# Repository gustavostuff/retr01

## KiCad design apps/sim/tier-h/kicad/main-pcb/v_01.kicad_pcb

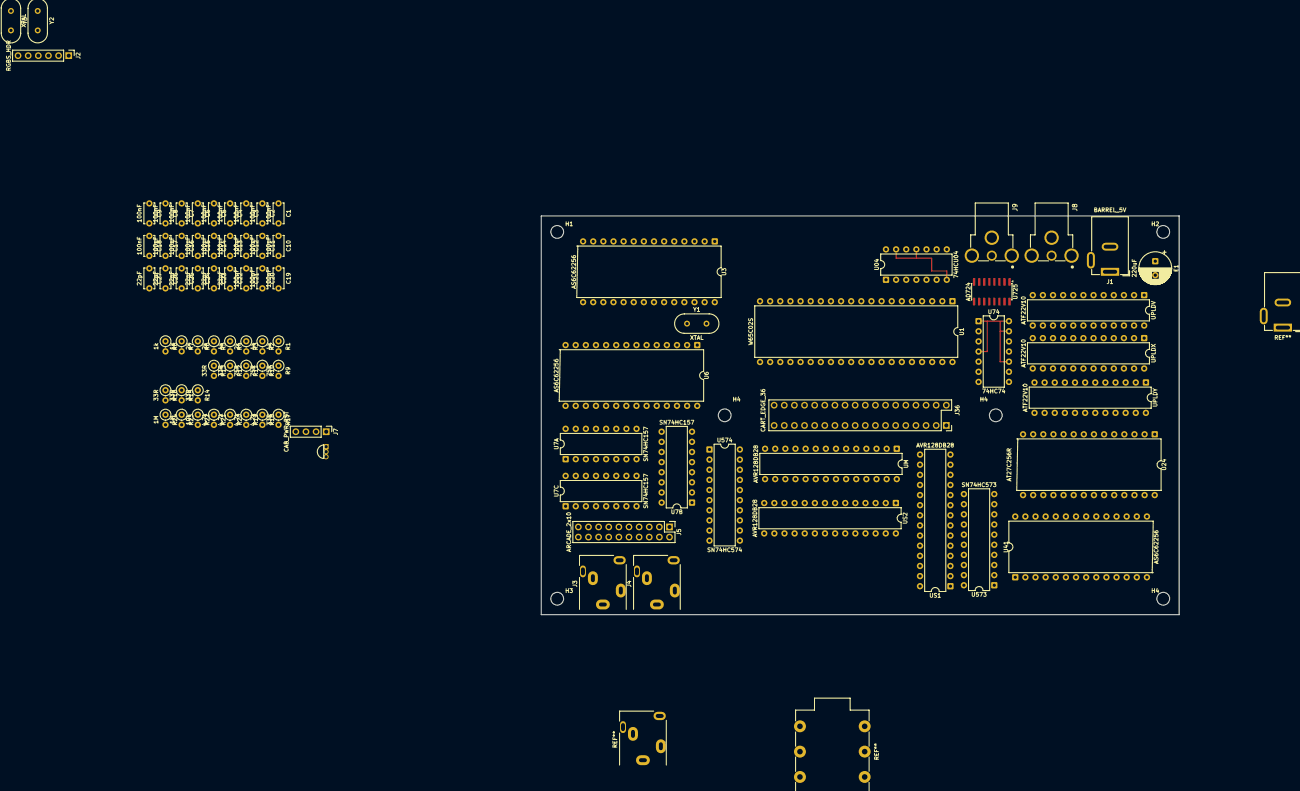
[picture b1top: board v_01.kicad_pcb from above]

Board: 2 copper layers, 160.0 x 100.0 mm, 90 parts (0 on the bottom side), 139 nets, no tracks yet.

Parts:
C1, C2, C3, C4, C5, C6, C7, C8, C9, C10, C11, C12, C13, C14, C15, C16, C17, C18, C19, C20, C21: 100nF; C_Disc_D5.0mm_W2.5mm_P5.00mm
C22, C23, C24, C25, C26, C27: 22pF; C_Disc_D5.0mm_W2.5mm_P5.00mm
E1: 220uF; CP_Radial_D8.0mm_P3.50mm
H1, H2, H3, H4, H4#2, H4#3: MountingHole_3.2mm_M3
J1: BARREL_5V; BarrelJack_GCT_DCJ200-10-A_Horizontal
J2: RGBS_HDR; PinHeader_1x06_P2.54mm_Vertical
J3: TRS_P1; Jack_3.5mm_CUI_SJ1-3515N_Horizontal
J4: TRS_P2; Jack_3.5mm_CUI_SJ1-3515N_Horizontal
J5: ARCADE_2x10; PinHeader_2x10_P2.54mm_Vertical
J7: CAB_PWR_RST; PinHeader_1x04_P2.54mm_Vertical
J8: RCJ-012; CUI_RCJ-014_Audio
J9: RCJ-014; CUI_RCJ-014
J36: CART_EDGE_36; EDAC_395_MoboSocket_2x18_2.54x5.08mm
R1, R2, R4: 4k; R_Axial_DIN0207_L6.3mm_D2.5mm_P2.54mm_Vertical
R3, R5, R6: 2k; R_Axial_DIN0207_L6.3mm_D2.5mm_P2.54mm_Vertical
R7, R8: 1k; R_Axial_DIN0207_L6.3mm_D2.5mm_P2.54mm_Vertical
R9, R10, R11: 75R; R_Axial_DIN0207_L6.3mm_D2.5mm_P2.54mm_Vertical
R12, R13, R14, R15, R16, R17: 33R; R_Axial_DIN0207_L6.3mm_D2.5mm_P2.54mm_Vertical
R18, R19, R20, R21: 4.7k; R_Axial_DIN0207_L6.3mm_D2.5mm_P2.54mm_Vertical
R22: 10k; R_Axial_DIN0207_L6.3mm_D2.5mm_P2.54mm_Vertical
R23, R24: 1M; R_Axial_DIN0207_L6.3mm_D2.5mm_P2.54mm_Vertical
U1: W65C02S; DIP-40_W15.24mm
U3, U6, U41: AS6C62256; DIP-28_W15.24mm
U04: 74HCU04; DIP-14_W7.62mm_74HCU04
U7A, U7B, U7C: SN74HC157; DIP-16_W7.62mm
U24: AT27C256R; DIP-28_W15.24mm
U74: 74HC74; DIP-14_W7.62mm_74HC74
U130: MCP130; TO-92_Inline
U573: SN74HC573; DIP-20_W7.62mm
U574: SN74HC574; DIP-20_W7.62mm
U725: AD724; SOIC-16_3.9x9.9mm_P1.27mm
UM: AVR128DB28; DIP-28_W7.62mm
UPLDV: ATF22V10; DIP-24_W7.62mm
UPLDX: ATF22V10; DIP-24_W7.62mm
UPLDY: ATF22V10; DIP-24_W7.62mm
US1, US2: AVR128DB28; DIP-28_W7.62mm
Y1, Y2, Y3: XTAL; Crystal_HC49-U_Vertical

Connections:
+5V: C1.1, C2.1, C3.1, C4.1, C5.1, C6.1, C7.1, C8.1, C9.1, C10.1, C11.1, C12.1, C13.1, C14.1, C15.1, C16.1, C17.1, C18.1, C19.1, C20.1, E1.1, J1.1 (+5V), J3.T (+5V), J4.T (+5V), J7.1, J36.3, J36.4, R18.1, R19.1, R20.1, R21.1, R22.1, U1.8 (VDD), U3.28 (VCC), U04.14 (VCC), U6.28 (VCC), U7A.16 (VCC), U7B.16 (VCC), U7C.16 (VCC), U24.28 (VCC), U41.28 (VCC), U74.14 (VCC), U130.2 (VDD), U573.20 (VCC), U574.20 (VCC), U725.1 (STND), U725.4 (APOS), U725.5 (ENCD), U725.14 (DPOS), U725.15 (VSYNC), UM.6, UM.14, UM.20, UPLDV.24, UPLDX.24, UPLDY.24, US1.6, US1.14, US1.20, US2.6, US2.14, US2.20
ALE_LE: U573.11 (LE), US1.16
AUDIO_OUT: J8.2 (SIGNAL), US2.17
CART_OE#_1: J36.24, R14.2
CART_SCL: J36.6, R17.2
CART_SDA: J36.5, R16.2
CART_WE#_1: J36.36, R15.2
CLK_10M: U74.5 (1Q), U74.11 (2CLK)
CLK_10M_INV: U74.2 (1D), U74.6 (1/Q)
CLK_21M: U04.4 (2Y), U74.3 (1CLK)
COMPOSITE_OUT: J9.2 (SIGNAL), U725.10 (COMP)
CPU_A0: J36.7, U1.9 (A0), U3.10 (A0), U7A.2 (I0a)
CPU_A1: J36.9, U1.10 (A1), U3.9 (A1), U7A.5 (I0b)
CPU_A2: J36.11, U1.11 (A2), U3.8 (A2), U7A.11 (I0c)
CPU_A3: J36.13, U1.12 (A3), U3.7 (A3), U7A.14 (I0d)
CPU_A4: J36.15, U1.13 (A4), U3.6 (A4), U7B.2 (I0a)
CPU_A5: J36.17, U1.14 (A5), U3.5 (A5), U7B.5 (I0b)
CPU_A6: J36.19, U1.15 (A6), U3.4 (A6), U7B.11 (I0c)
CPU_A7: J36.21, U1.16 (A7), U3.3 (A7), U7B.14 (I0d)
CPU_A8: J36.23, U1.17 (A8), U3.25 (A8), U7C.2 (I0a)
CPU_A9: J36.25, U1.18 (A9), U3.24 (A9), U7C.5 (I0b)
CPU_A10: J36.27, U1.19 (A10), U3.21 (A10), U7C.11 (I0c)
CPU_A11: J36.29, U1.20 (A11), U3.23 (A11), U7C.14 (I0d)
CPU_A12: J36.31, U1.22 (A12), U3.2 (A12)
CPU_A13: J36.33, U1.23 (A13), U3.26 (A13)
CPU_A14: U1.24 (A14), U3.1 (A14)
CPU_D0: J36.8, U1.33 (D0), U3.11 (Q0), U6.11 (Q0), U574.2 (D0), UM.22
CPU_D1: J36.10, U1.32 (D1), U3.12 (Q1), U6.12 (Q1), U574.3 (D1), UM.23
CPU_D2: J36.12, U1.31 (D2), U3.13 (Q2), U6.13 (Q2), U574.4 (D2), UM.26
CPU_D3: J36.14, U1.30 (D3), U3.15 (Q3), U6.15 (Q3), U574.5 (D3), UM.27
CPU_D4: J36.16, U1.29 (D4), U3.16 (Q4), U6.16 (Q4), U574.6 (D4), UM.28
CPU_D5: J36.18, U1.28 (D5), U3.17 (Q5), U6.17 (Q5), U574.7 (D5), UM.1
CPU_D6: J36.20, U1.27 (D6), U3.18 (Q6), U6.18 (Q6), U574.8 (D6), UM.12
CPU_D7: J36.22, U1.26 (D7), U3.19 (Q7), U6.19 (Q7), U574.9 (D7), UM.13
CPU_IRQ#: U1.4 (IRQB), UPLDY.1
CPU_PHI2: R12.2, U1.37 (PHI2)
CPU_RDY: R21.2, U1.2 (RDY), UM.8
CPU_RES#: J7.3, R22.2, U1.40 (RESB), U130.1 (RESET#)
CSYNC: J2.4 (CSYNC), U725.16 (HSYNC), UPLDV.14
DOT: R13.1, U74.9 (2Q)
DOT_INV: U74.8 (2/Q), U74.12 (2D)
FSC_FIN: C23.1, U725.3 (FIN), Y3.1
FSC_XTAL: C24.1, Y3.2
GND: C1.2, C2.2, C3.2, C4.2, C5.2, C6.2, C7.2, C8.2, C9.2, C10.2, C11.2, C12.2, C13.2, C14.2, C15.2, C16.2, C17.2, C18.2, C19.2, C20.2, C21.2, C22.2, C23.2, C24.2, C25.2, C26.2, C27.2, E1.2, J1.2 (GND), J1.3 (GND), J3.S (GND), J4.S (GND), J5.17, J5.18, J5.19, J5.20, J7.2, J7.4, J8.1A (GND), J8.1B (GND), J8.1C (GND), J9.1A (GND), J9.1B (GND), J9.1C (GND), J36.1, J36.2, J36.35, R9.2, R10.2, R11.2, U1.21 (VSS), U3.14 (GND), U04.7 (GND), U6.14 (GND), U7A.8 (GND), U7B.8 (GND), U7C.8 (GND), U24.2 (A12), U24.3 (A7), U24.4 (A6), U24.14 (GND), U24.20 (~CE), U24.21 (A10), U24.22 (~OE), U24.23 (A11), U24.24 (A9), U24.25 (A8), U24.26 (A13), U41.14 (GND), U74.7 (GND), U130.3 (VSS), U573.1 (OE#), U573.10 (GND), U574.1 (OE#), U574.10 (GND), U725.2 (AGND), U725.12 (SELECT), U725.13 (DGND), UM.15, UM.21, UPLDV.12, UPLDX.12, UPLDY.12, US1.15, US1.21, US2.15, US2.21
LB_A0: U41.10 (A0), U573.19 (Q7)
LB_A1: U41.9 (A1), U573.18 (Q6)
LB_A2: U41.8 (A2), U573.17 (Q5)
LB_A3: U41.7 (A3), U573.16 (Q4)
LB_A4: U41.6 (A4), U573.15 (Q3)
LB_A5: U41.5 (A5), U573.14 (Q2)
LB_A6: U41.4 (A6), U573.13 (Q1)
LB_A7: U41.3 (A7), U573.12 (Q0)
LINEBUF_WE#: U41.27 (~WE), US1.17
MCU_SCL: R17.1, R20.2, UM.25
MCU_SDA: R16.1, R19.2, UM.24
PAD_DATA_BUS: R18.2, US2.16
PHI2: R12.1, U04.8 (4Y)
PROM_O0: R8.1, U24.11 (D0)
PROM_O1: R7.1, U24.12 (D1)
PROM_O2: R6.1, U24.13 (D2)
PROM_O3: R5.1, U24.15 (D3)
PROM_O4: R4.1, U24.16 (D4)
PROM_O5: R3.1, U24.17 (D5)
PROM_O6: R2.1, U24.18 (D6)
PROM_O7: R1.1, U24.19 (D7)
SCROLL_CLK_1: J3.R (DATA), J3.RN (NC), J3.TN (NC), J4.R (DATA), J4.RN (NC), J4.TN (NC), U04.10 (5Y), U04.12 (6Y), U574.11 (CLK)
SIG_J5_P2_TO_US2_P2: J5.2, US2.2
SIG_J5_P3_TO_US2_P23: J5.3, US2.23
SIG_J5_P4_TO_US2_P3: J5.4, US2.3
SIG_J5_P6_TO_US2_P4: J5.6, US2.4
SIG_J5_P7_TO_US2_P25: J5.7, US2.25
SIG_J5_P8_TO_US2_P5: J5.8, US2.5
SIG_J5_P10_TO_US2_P7: J5.10, US2.7
SIG_J5_P12_TO_US2_P8: J5.12, US2.8
SIG_J5_P14_TO_US2_P9: J5.14, US2.9
SIG_J5_P16_TO_US2_P18: J5.16, US2.18
SIG_U6_P3_TO_U7B_P12: U6.3 (A7), U7B.12 (Zd)
SIG_U6_P6_TO_U7B_P4: U6.6 (A4), U7B.4 (Za)
SIG_U6_P7_TO_U7A_P12: U6.7 (A3), U7A.12 (Zd)
SIG_U6_P8_TO_U7A_P9: U6.8 (A2), U7A.9 (Zc)
SIG_U6_P10_TO_U7A_P4: U6.10 (A0), U7A.4 (Za)
SIG_U6_P21_TO_U7C_P9: U6.21 (A10), U7C.9 (Zc)
SIG_U6_P23_TO_U7C_P12: U6.23 (A11), U7C.12 (Zd)
SIG_U6_P25_TO_U7C_P4: U6.25 (A8), U7C.4 (Za)
SIG_U7A_P7_TO_U6_P9: U6.9 (A1), U7A.7 (Zb)
SIG_U7B_P7_TO_U6_P5: U6.5 (A5), U7B.7 (Zb)
SIG_U7B_P9_TO_U6_P4: U6.4 (A6), U7B.9 (Zc)
SIG_U7C_P7_TO_U6_P24: U6.24 (A9), U7C.7 (Zb)
SIG_U24_P6_TO_UPLDV_P19: U24.6 (A4), UPLDV.19
SIG_U41_P1_TO_US1_P9: U41.1 (A14), US1.9
SIG_U41_P2_TO_US1_P7: U41.2 (A12), US1.7
SIG_U41_P11_BUS: U41.11 (Q0), U573.2 (D0), US1.22
SIG_U41_P13_BUS: U41.13 (Q2), U573.4 (D2), US1.24
SIG_U41_P17_BUS: U41.17 (Q5), U573.7 (D5), US1.27
SIG_U41_P18_BUS: U41.18 (Q6), U573.8 (D6), US1.28
SIG_U41_P23_TO_US1_P5: U41.23 (A11), US1.5
SIG_U41_P24_TO_US1_P3: U41.24 (A9), US1.3
SIG_U573_P3_BUS: U41.12 (Q1), U573.3 (D1), US1.23
SIG_U573_P5_BUS: U41.15 (Q3), U573.5 (D3), US1.25
SIG_U573_P9_BUS: U41.19 (Q7), U573.9 (D7), US1.1
SIG_UM_P18_TO_US1_P18: UM.18, US1.18
SIG_UPLDV_P15_TO_U24_P10: U24.10 (A0), UPLDV.15
SIG_UPLDV_P16_TO_U24_P9: U24.9 (A1), UPLDV.16
SIG_UPLDV_P17_TO_U24_P8: U24.8 (A2), UPLDV.17
SIG_UPLDV_P18_TO_U24_P7: U24.7 (A3), UPLDV.18
SIG_UPLDV_P20_TO_U24_P5: U24.5 (A5), UPLDV.20
SIG_UPLDX_P1_TO_R13_P2: R13.2, UPLDX.1
SIG_UPLDX_P14_TO_UPLDY_P3: UPLDX.14, UPLDY.3
SIG_UPLDX_P16_TO_UPLDY_P5: UPLDX.16, UPLDY.5
SIG_UPLDX_P17_TO_UPLDY_P6: UPLDX.17, UPLDY.6
SIG_UPLDX_P18_TO_UPLDY_P7: UPLDX.18, UPLDY.7
SIG_UPLDX_P20_TO_UPLDY_P9: UPLDX.20, UPLDY.9
SIG_UPLDY_P2_TO_UPLDX_P13: UPLDX.13, UPLDY.2
SIG_UPLDY_P4_TO_UPLDX_P15: UPLDX.15, UPLDY.4
SIG_UPLDY_P8_TO_UPLDX_P19: UPLDX.19, UPLDY.8
SIG_US1_P2_TO_U41_P25: U41.25 (A8), US1.2
SIG_US1_P4_TO_U41_P21: U41.21 (A10), US1.4
SIG_US1_P8_TO_U41_P26: U41.26 (A13), US1.8
SIG_US1_P26_BUS: U41.16 (Q4), U573.6 (D4), US1.26
SIG_US2_P1_TO_J5_P15: J5.15, US2.1
SIG_US2_P22_TO_J5_P1: J5.1, US2.22
SIG_US2_P24_TO_J5_P5: J5.5, US2.24
SIG_US2_P26_TO_J5_P9: J5.9, US2.26
SIG_US2_P27_TO_J5_P11: J5.11, US2.27
SIG_US2_P28_TO_J5_P13: J5.13, US2.28
SPI_MISO: UM.3, US1.11, US2.11
SPI_MOSI: UM.2, US1.10, US2.10
SPI_SCK: UM.4, US1.12, US2.12
SS_S1#: UM.5, US1.13
SS_S2#: UM.11, US2.13
U04_SPARE_IN: U04.11 (5A), U04.13 (6A)
U74_PRE_CLR#: U74.1 (1CLR#), U74.4 (1PRE#), U74.10 (2PRE#), U74.13 (2CLR#)
VIDEO_BLUE: J2.3 (B), R7.2, R8.2, R11.1, U725.8 (BIN)
VIDEO_GREEN: J2.2 (G), R4.2, R5.2, R6.2, R10.1, U725.7 (GIN)
VIDEO_RED: J2.1 (R), R1.2, R2.2, R3.2, R9.1, U725.6 (RIN)
XTAL_10M_IN: C25.1, R23.1, U04.5 (3A), Y1.1
XTAL_10M_OUT: C26.1, R23.2, U04.6 (3Y), U04.9 (4A), Y1.2
XTAL_21M_OUT: C22.1, R24.2, U04.2 (1Y), U04.3 (2A), Y2.2
XTAL_DOT_IN: C21.1, R24.1, U04.1 (1A), Y2.1

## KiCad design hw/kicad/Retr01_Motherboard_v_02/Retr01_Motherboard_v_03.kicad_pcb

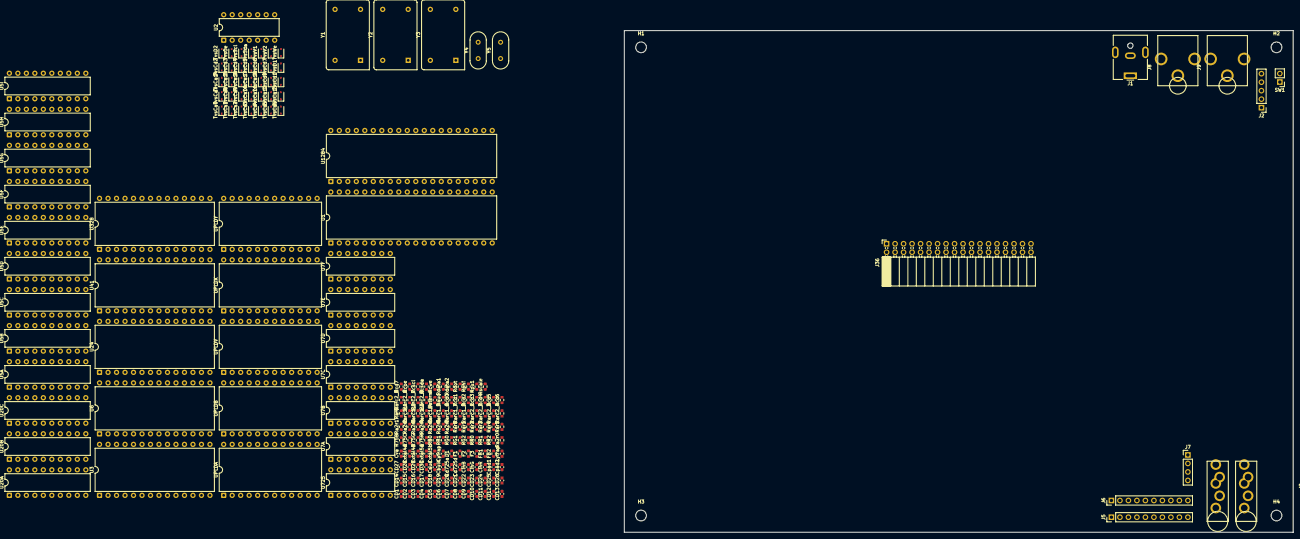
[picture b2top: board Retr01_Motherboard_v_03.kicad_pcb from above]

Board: 4 copper layers, 200.0 x 150.0 mm, 202 parts (0 on the bottom side), 213 nets, no tracks yet.

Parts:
CD1, CD2, CD3, CD4, CD5, CD6, CD7, CD8, CD9, CD10, CD11, CD12, CD13, CD14, CD15, CD16, CD17, CD18, CD19, CD20, CD21, CD22, CD23, CD24, CD25, CD26, CD27, CD28, CD29, CD30: C_100N; C_0603_1608Metric
Caud: C_10U_AUD; C_0603_1608Metric
Cbulk: C_BULK; C_0603_1608Metric
Cd725a, Cd725d: C_100N; C_0603_1608Metric
CinB: C_100N; C_0603_1608Metric
CinG: C_100N; C_0603_1608Metric
CinR: C_100N; C_0603_1608Metric
Cpad1, Cpad2: C_100N; C_0603_1608Metric
Cva: C_10U; C_0603_1608Metric
Cxtal4a, Cxtal4b, Cxtal5a, Cxtal5b: C_22P; C_0603_1608Metric
Cytrap: C_100N; C_0603_1608Metric
D1: SCHOTTKY; R_0603_1608Metric
F1, F2, F3: PPTC; R_0603_1608Metric
FB1, FB2: FERRITE; R_0603_1608Metric
H1, H2, H3, H4: MountingHole_3.2mm_M3
J1: BARREL_5V; BarrelJack_CUI_PJ-063AH_Horizontal
J2: RGBS_HDR; PinHeader_1x05_P2.54mm_Vertical
J3: TRS_P1; Jack_3.5mm_Switchcraft_35RAPC2BVN4_Vertical
J4: TRS_P2; Jack_3.5mm_Switchcraft_35RAPC2BVN4_Vertical
J5: ARCADE_P1; PinHeader_1x10_P2.54mm_Vertical
J6: ARCADE_P2; PinHeader_1x10_P2.54mm_Vertical
J7: CAB_PWR_RST; PinHeader_1x04_P2.54mm_Vertical
J8: AUDIO_OUT; CUI_RCJ-01x_Vertical
J9: COMPOSITE_OUT; CUI_RCJ-01x_Vertical
J36: CART_EDGE_36; PinSocket_2x18_P2.54mm_Horizontal
Lytrap: L_YTRAP; L_0603_1608Metric
R75B, R75C, R75G, R75R: R_75; R_0603_1608Metric
RB0: R_2K; R_0603_1608Metric
RB1: R_1K; R_0603_1608Metric
RG0: R_4K; R_0603_1608Metric
RG1: R_2K; R_0603_1608Metric
RG2: R_1K; R_0603_1608Metric
RR0: R_4K; R_0603_1608Metric
RR1: R_2K; R_0603_1608Metric
RR2: R_1K; R_0603_1608Metric
Ra2r0, Ra2r1, Ra2r2, Ra2r3, Ra2r4, Ra2r5, Ra2r6, Ra2r7: R_20K; R_0603_1608Metric
Rar0, Rar1, Rar2, Rar3, Rar4, Rar5, Rar6: R_10K; R_0603_1608Metric
Rarc1_1, Rarc1_2, Rarc1_3, Rarc1_4, Rarc1_5, Rarc1_6, Rarc1_7, Rarc1_8, Rarc2_1, Rarc2_2, Rarc2_3, Rarc2_4, Rarc2_5, Rarc2_6, Rarc2_7, Rarc2_8: R_47; R_0603_1608Metric
Raterm: R_20K; R_0603_1608Metric
Raud: R_1K; R_0603_1608Metric
Rcd0, Rcd1, Rcd2, Rcd3, Rcd4, Rcd5, Rcd6, Rcd7: R_33; R_0603_1608Metric
Rcoe: R_33; R_0603_1608Metric
Rcscl: R_33; R_0603_1608Metric
Rcsda: R_33; R_0603_1608Metric
Rcwe: R_33; R_0603_1608Metric
Rdata1, Rdata2: R_47; R_0603_1608Metric
Rdot: R_33; R_0603_1608Metric
Rphi: R_33; R_0603_1608Metric
Rpu1: R_4K7; R_0603_1608Metric
Rscale: R_10K; R_0603_1608Metric
SW1: SCALE_SW; PinHeader_1x02_P2.54mm_Vertical
TvsCa0, TvsCa1, TvsCa2, TvsCa3, TvsCa4, TvsCa5, TvsCa6, TvsCa7, TvsCa8, TvsCa9, TvsCa10, TvsCa11, TvsCa12, TvsCa13, TvsCa14, TvsCa15, TvsCa16, TvsCa17, TvsCa18: TVS_5V; D_SOD-323
TvsCd0, TvsCd1, TvsCd2, TvsCd3, TvsCd4, TvsCd5, TvsCd6, TvsCd7: TVS_5V; D_SOD-323
TvsD1, TvsD2: TVS_5V; D_SOD-323
TvsOe: TVS_5V; D_SOD-323
TvsScl: TVS_5V; D_SOD-323
TvsSda: TVS_5V; D_SOD-323
TvsV1, TvsV2: TVS_5V; D_SOD-323
TvsWe: TVS_5V; D_SOD-323
U1: W65C02S; DIP-40_W15.24mm
U2: SN74HC14; DIP-14_W7.62mm
U3, U6, U41: AS6C62256; DIP-28_W15.24mm
U5A, U5B, U5C, U5D, U5E, U5F, U5G, U5H, U5I: SN74HC573; DIP-20_W7.62mm
U7A, U7B, U7C, U7D, U7E, U7F: SN74HC157; DIP-16_W7.62mm
U20A, U20B, U20C: SN74HC245; DIP-20_W7.62mm
U24: AT27C256R; DIP-28_W15.24mm
U328: ATmega328P; DIP-28_W15.24mm
U725: AD725; DIP-16_W7.62mm
U1284: ATmega1284P; DIP-40_W15.24mm
UPLDA: ATF22V10; DIP-24_W15.24mm
UPLDB: ATF22V10; DIP-24_W15.24mm
UPLDV: ATF22V10; DIP-24_W15.24mm
UPLDX: ATF22V10; DIP-24_W15.24mm
UPLDY: ATF22V10; DIP-24_W15.24mm
Y1: OSC8M; Oscillator_DIP-14
Y2: OSC_DOT; Oscillator_DIP-14
Y3: OSC_4FSC; Oscillator_DIP-14
Y4: XTAL_20M; Crystal_HC49-U_Vertical
Y5: XTAL_16M; Crystal_HC49-U_Vertical

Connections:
+5V: CD1.1, CD2.1, CD3.1, CD4.1, CD5.1, CD6.1, CD7.1, CD8.1, CD9.1, CD10.1, CD11.1, CD12.1, CD13.1, CD14.1, CD15.1, CD16.1, CD17.1, CD18.1, CD19.1, CD20.1, CD21.1, CD22.1, CD23.1, CD24.1, CD25.1, CD26.1, CD27.1, CD28.1, CD29.1, CD30.1, Cbulk.1, Cd725a.1, Cd725d.1, Cva.1, F2.1, F3.1, FB1.2, FB2.1, FB2.2, J7.1, J36.2, J36.20, Rpu1.1, SW1.2, U1.8, U2.14, U3.28, U5A.20, U5B.20, U5C.20, U5D.20, U5E.20, U5F.20, U5G.20, U5H.20, U5I.20, U6.28, U7A.16, U7B.16, U7C.16, U7D.16, U7E.16, U7F.16, U20A.20, U20B.20, U20C.20, U24.28, U41.28, U328.7, U725.1, U725.4, U725.5, U725.14, U725.15, U1284.10, UPLDA.24, UPLDB.24, UPLDV.24, UPLDX.24, UPLDY.24, Y1.1, Y1.14, Y2.1, Y2.14, Y3.1, Y3.14
AD725_BIN: CinB.2, U725.8
AD725_GIN: CinG.2, U725.7
AD725_RIN: CinR.2, U725.6
ASUM0: Ra2r0.2, Rar0.1, Raterm.1
ASUM1: Ra2r1.2, Rar0.2, Rar1.1
ASUM2: Ra2r2.2, Rar1.2, Rar2.1
ASUM3: Ra2r3.2, Rar2.2, Rar3.1
ASUM4: Ra2r4.2, Rar3.2, Rar4.1
ASUM5: Ra2r5.2, Rar4.2, Rar5.1
ASUM6: Ra2r6.2, Rar5.2, Rar6.1
AUD0: Ra2r0.1, U328.14
AUD1: Ra2r1.1, U328.15
AUD2: Ra2r2.1, U328.16
AUD3: Ra2r3.1, U328.17
AUD4: Ra2r4.1, U328.18
AUD5: Ra2r5.1, U328.19
AUD6: Ra2r6.1, U328.23
AUD7: Ra2r7.1, U328.24
AUDIO_OUT: Caud.2, J8.1
AUDIO_SUM: Caud.1, Ra2r7.2, Rar6.2, Raud.1
BEAM_LB_A9: U7D.6, U7E.6, U7F.6, UPLDX.16, UPLDY.3
BEAM_LB_A10: U7D.10, U7E.10, U7F.10, UPLDX.17, UPLDY.4
BEAM_LB_A11: U7D.13, U7E.13, U7F.13, UPLDX.18, UPLDY.5
BEAM_Y0: U7D.3, U7E.3, U7F.3, UPLDX.15, UPLDY.2
BEAM_Y4: UPLDX.19, UPLDY.6
BEAM_Y5: UPLDX.20, UPLDY.7
BEAM_Y6: UPLDX.21, UPLDY.8
BEAM_Y7: UPLDX.22, UPLDY.9
CART_A0: J36.4, TvsCa0.1, U1.9, U3.10, UPLDA.2
CART_A5: J36.9, TvsCa5.1, U1.14, U3.5, UPLDA.7
CART_A6: J36.10, TvsCa6.1, U1.15, U3.4, UPLDA.8
CART_A7: J36.11, TvsCa7.1, U1.16, U3.3, UPLDA.9
CART_A8: J36.12, TvsCa8.1, U1.17, U3.25
CART_A11: J36.15, TvsCa11.1, U1.20, U3.23
CART_A13: J36.17, TvsCa13.1, U1.23, U3.26
CART_A14: J36.31, TvsCa14.1, U5G.19
CART_A15: J36.32, TvsCa15.1, U5H.18
CART_A16: J36.33, TvsCa16.1, U5I.17
CART_A17: J36.34, TvsCa17.1, U5I.16
CART_A18: J36.35, TvsCa18.1, U5I.15
CART_D0: J36.22, Rcd0.2, TvsCd0.1
CART_D0_MCU: Rcd0.1, U20C.18
CART_D1: J36.23, Rcd1.2, TvsCd1.1
CART_D1_MCU: Rcd1.1, U20C.17
CART_D2: J36.24, Rcd2.2, TvsCd2.1
CART_D2_MCU: Rcd2.1, U20C.16
CART_D3: J36.25, Rcd3.2, TvsCd3.1
CART_D3_MCU: Rcd3.1, U20C.15
CART_D4: J36.26, Rcd4.2, TvsCd4.1
CART_D4_MCU: Rcd4.1, U20C.14
CART_D5: J36.27, Rcd5.2, TvsCd5.1
CART_D5_MCU: Rcd5.1, U20C.13
CART_D6: J36.28, Rcd6.2, TvsCd6.1
CART_D6_MCU: Rcd6.1, U20C.12
CART_D7: J36.29, Rcd7.2, TvsCd7.1
CART_D7_MCU: Rcd7.1, U20C.11
CART_OE_MCU: Rcoe.1, UPLDB.20
CART_OE_N: J36.30, Rcoe.2, TvsOe.1
CART_WE_MCU: Rcwe.1, UPLDB.21
CART_WE_N: J36.36, Rcwe.2, TvsWe.1
COMPOSITE_OUT: J9.1, R75C.2
COMP_RAW: R75C.1, U725.10
CPU_A9: J36.13, TvsCa9.1, U1.18, U3.24
CPU_A10: J36.14, TvsCa10.1, U1.19, U3.21
CPU_A12: J36.16, TvsCa12.1, U1.22, U3.2
CPU_A14: U1.24, U3.1
CPU_A_LO1: J36.5, TvsCa1.1, U1.10, U3.9, UPLDA.3
CPU_A_LO2: J36.6, TvsCa2.1, U1.11, U3.8, UPLDA.4
CPU_A_LO3: J36.7, TvsCa3.1, U1.12, U3.7, UPLDA.5
CPU_A_LO4: J36.8, TvsCa4.1, U1.13, U3.6, UPLDA.6
CPU_BE: U1.36, UPLDA.10
CPU_D0: U1.33, U3.11, U5A.2, U5B.2, U5C.2, U5D.2, U5E.2, U5F.2, U5G.2, U5H.2, U5I.2, U6.11, U7A.2, U7A.3, U20A.2, U20A.18, U20C.2, U328.2, U1284.24, UPLDB.2
CPU_D3: U1.30, U3.15, U5A.5, U5B.5, U5C.5, U5D.5, U5E.5, U5F.5, U5G.5, U5H.5, U5I.5, U6.15, U7A.13, U7A.14, U20A.5, U20A.15, U20C.5, U328.5, U1284.27, UPLDB.5
CPU_D4: U1.29, U3.16, U5A.6, U5B.6, U5C.6, U5D.6, U5E.6, U5F.6, U5G.6, U5H.6, U5I.6, U6.16, U7B.2, U7B.3, U20A.6, U20A.14, U20C.6, U328.6, U1284.28, UPLDB.6
CPU_RWB: U1.34, UPLDA.11
CPU_VA2: U1.31, U3.13, U5A.4, U5B.4, U5C.4, U5D.4, U5E.4, U5F.4, U5G.4, U5H.4, U5I.4, U6.13, U7A.10, U7A.11, U20A.4, U20A.16, U20C.4, U328.4, U1284.26, UPLDB.4
CPU_VA6: U1.27, U3.18, U5A.8, U5B.8, U5C.8, U5D.8, U5E.8, U5F.8, U5G.8, U5H.8, U5I.8, U6.18, U7B.10, U7B.11, U20A.8, U20A.12, U20C.8, U328.12, U1284.20, UPLDB.8
CPU_VA8: U7C.2, U7C.3, UPLDB.10
CSYNC: J2.4, U725.16, UPLDV.14
DIR_CART245: U20C.1, UPLDB.18
DIR_CPU245: U7C.13, U7C.14, U20A.1, UPLDB.14
DIR_VID245: U6.26, U20B.1, UPLDB.16
DOT_CLK: Rdot.2, UPLDX.1
DOT_SRC: Rdot.1, Y2.8
FSC4: U725.3, Y3.8
GND: CD1.2, CD2.2, CD3.2, CD4.2, CD5.2, CD6.2, CD7.2, CD8.2, CD9.2, CD10.2, CD11.2, CD12.2, CD13.2, CD14.2, CD15.2, CD16.2, CD17.2, CD18.2, CD19.2, CD20.2, CD21.2, CD22.2, CD23.2, CD24.2, CD25.2, CD26.2, CD27.2, CD28.2, CD29.2, CD30.2, Cbulk.2, Cd725a.2, Cd725d.2, Cpad1.2, Cpad2.2, Cva.2, Cxtal4a.2, Cxtal4b.2, Cxtal5a.2, Cxtal5b.2, Cytrap.2, J1.2, J1.MP, J2.5, J3.1, J4.1, J5.9, J5.10, J6.9, J6.10, J7.2, J7.4, J8.2, J9.2, J36.1, J36.18, J36.19, R75B.2, R75G.2, R75R.2, Raterm.2, Rscale.2, TvsCa0.2, TvsCa1.2, TvsCa2.2, TvsCa3.2, TvsCa4.2, TvsCa5.2, TvsCa6.2, TvsCa7.2, TvsCa8.2, TvsCa9.2, TvsCa10.2, TvsCa11.2, TvsCa12.2, TvsCa13.2, TvsCa14.2, TvsCa15.2, TvsCa16.2, TvsCa17.2, TvsCa18.2, TvsCd0.2, TvsCd1.2, TvsCd2.2, TvsCd3.2, TvsCd4.2, TvsCd5.2, TvsCd6.2, TvsCd7.2, TvsD1.2, TvsD2.2, TvsOe.2, TvsScl.2, TvsSda.2, TvsV1.2, TvsV2.2, TvsWe.2, U1.21, U3.14, U5A.10, U5B.10, U5C.10, U5D.10, U5E.10, U5F.10, U5G.10, U5H.10, U5I.10, U6.14, U7A.8, U7B.8, U7C.8, U7D.8, U7E.8, U7F.8, U20A.10, U20B.10, U20C.10, U24.14, U41.14, U328.8, U725.2, U725.13, U1284.11, UPLDA.12, UPLDB.12, UPLDV.12, UPLDX.12, UPLDY.12, Y1.7, Y2.7, Y3.7
I2C_SCL: J36.21, Rcscl.2, TvsScl.1
I2C_SCL_MCU: Rcscl.1, U1284.22
I2C_SDA: J36.3, Rcsda.2, TvsSda.1
I2C_SDA_MCU: Rcsda.1, U1284.23
IRQ_N: U1.4, UPLDY.22
LB_A0: U7D.4, U41.10
LB_A1: U7D.7, U41.9
LB_A2: U7D.9, U41.8
LB_A3: U7D.12, U41.7
LB_A4: U7E.4, U41.6
LB_A5: U7E.7, U41.5
LB_A6: U7E.9, U41.4
LB_A7: U7E.12, U41.3
LB_A8: U7F.4, U41.25
LB_A9: U7F.7, U41.24
LB_A10: U7F.9, U41.21
LB_A11: U7F.12, U41.23
LB_MUX_AB: U7D.1, U7E.1, U7F.1, U1284.17
LB_MUX_G_N: U7D.15, U7E.15, U7F.15
MCU_LB_A0: Rarc2_1.2, U7D.2, U7F.2, U1284.1
MCU_LB_A2: Rarc2_3.2, U7D.11, U7F.11, U1284.3
MCU_LB_A4: Rarc2_5.2, U7E.2, U41.2, U1284.5
MUX_G_N: U7A.15, U7B.15, U7C.15
NMI_N: U1.6, UPLDX.14
OE_CART245: U20C.19, UPLDB.19
OE_CPU245: U6.2, U20A.19, UPLDB.15
OE_VID245: U6.1, U20B.19, UPLDB.17
P1_COIN: Rarc1_7.2, U1284.34
P1_COIN_J: J5.7, Rarc1_7.1
P1_DOWN: Rarc1_3.2, U1284.38
P1_DOWN_J: J5.3, Rarc1_3.1
P1_LEFT: Rarc1_2.2, U1284.39
P1_LEFT_J: J5.2, Rarc1_2.1
P1_RIGHT: Rarc1_1.2, U1284.40
P1_RIGHT_J: J5.1, Rarc1_1.1
P1_START: Rarc1_8.2, U1284.33
P1_START_J: J5.8, Rarc1_8.1
P1_UP: Rarc1_4.2, U1284.37
P1_UP_J: J5.4, Rarc1_4.1
P1_X: Rarc1_5.2, U1284.36
P1_X_J: J5.5, Rarc1_5.1
P1_Y: Rarc1_6.2, U1284.35
P1_Y_J: J5.6, Rarc1_6.1
P2_COIN: Rarc2_7.2, U7E.11, U41.1, U1284.7
P2_COIN_J: J6.7, Rarc2_7.1
P2_DOWN_J: J6.3, Rarc2_3.1
P2_LEFT: Rarc2_2.2, U7D.5, U7F.5, U1284.2
P2_LEFT_J: J6.2, Rarc2_2.1
P2_RIGHT_J: J6.1, Rarc2_1.1
P2_START: Rarc2_8.2, U7E.14, U1284.8
P2_START_J: J6.8, Rarc2_8.1
P2_UP: Rarc2_4.2, U7D.14, U7F.14, U1284.4
P2_UP_J: J6.4, Rarc2_4.1
P2_X_J: J6.5, Rarc2_5.1
P2_Y: Rarc2_6.2, U7E.5, U41.26, U1284.6
P2_Y_J: J6.6, Rarc2_6.1
PAD_DATA: Rdata1.1, Rdata2.1, Rpu1.2, U1284.16
PAD_DATA_P1: J3.2, Rdata1.2, TvsD1.1
PAD_DATA_P2: J4.2, Rdata2.2, TvsD2.1
PAD_VCC_P1: Cpad1.1, F2.2, J3.4, TvsV1.1
PAD_VCC_P2: Cpad2.1, F3.2, J4.4, TvsV2.1
PHI2: Rphi.2, U1.37, U2.1, U2.2, U7A.1, U7B.1, U7C.1
PHI2_SRC: Rphi.1, Y1.8
PPU_VA1: U1.32, U3.12, U5A.3, U5B.3, U5C.3, U5D.3, U5E.3, U5F.3, U5G.3, U5H.3, U5I.3, U6.12, U7A.5, U7A.6, U20A.3, U20A.17, U20C.3, U328.3, U1284.25, UPLDB.3
PPU_VA5: U1.28, U3.17, U5A.7, U5B.7, U5C.7, U5D.7, U5E.7, U5F.7, U5G.7, U5H.7, U5I.7, U6.17, U7B.5, U7B.6, U20A.7, U20A.13, U20C.7, U328.11, U1284.29, UPLDB.7
PPU_VA7: U1.26, U3.19, U5A.9, U5B.9, U5C.9, U5D.9, U5E.9, U5F.9, U5G.9, U5H.9, U5I.9, U6.19, U7B.13, U7B.14, U20A.9, U20A.11, U20C.9, U328.13, U1284.21, UPLDB.9
PPU_VA9: U7C.5, U7C.6, UPLDB.11
PPU_VA10: U7C.10, U7C.11, UPLDB.13
PROM_A0: U24.10, UPLDV.2
PROM_A1: U24.9, UPLDV.3
PROM_A2: U24.8, UPLDV.4
PROM_A3: U24.7, UPLDV.5
PROM_A4: U24.6, UPLDV.6
PROM_A5: U24.5, UPLDV.7
PROM_D0: RB0.1, U24.11
PROM_D1: RB1.1, U24.12
PROM_D2: RG0.1, U24.13
PROM_D3: RG1.1, U24.15
PROM_D4: RG2.1, U24.16
PROM_D5: RR0.1, U24.17
PROM_D6: RR1.1, U24.18
PROM_D7: RR2.1, U24.19
RASTER_Y0: U5D.19, UPLDY.14
RASTER_Y1: U5D.18, UPLDY.15
RASTER_Y2: U5D.17, UPLDY.16
RASTER_Y3: U5D.16, UPLDY.17
RASTER_Y4: U5D.15, UPLDY.18
RASTER_Y5: U5D.14, UPLDY.19
RASTER_Y6: U5D.13, UPLDY.20
RASTER_Y7: U5D.12, UPLDY.21
RESET_N: J7.3, U1.40, U2.3, UPLDX.13
SCALE_1X: Rscale.1, SW1.1, UPLDV.13
SEL_FE02: U5B.11, U1284.19, UPLDA.15
SEL_FE03: U5C.11, UPLDA.16
SEL_FE04: U5D.11, UPLDA.17
SEL_FE05: U5E.11, UPLDA.18
SEL_FE06: U5A.11, U1284.18, UPLDA.14
SEL_FE08: U5F.11, UPLDA.19
SEL_FE11: UPLDA.23, UPLDB.22, UPLDB.23
SEL_FE90: U5G.11, UPLDA.20
SEL_FE91: U5H.11, UPLDA.21
SEL_FE92: U5I.11, UPLDA.22
VIDEO_B: CinB.1, J2.3, R75B.1, RB0.2, RB1.2
VIDEO_G: CinG.1, J2.2, R75G.1, RG0.2, RG1.2, RG2.2
VIDEO_R: CinR.1, J2.1, R75R.1, RR0.2, RR1.2, RR2.2
VIN_FUSED: F1.2, FB1.1
VIN_PROT: D1.2, F1.1
VIN_RAW: D1.1, J1.1
VRAM_A0: U6.10, U7A.4
VRAM_A1: U6.9, U7A.7
VRAM_A2: U6.8, U7A.9
VRAM_A3: U6.7, U7A.12
VRAM_A4: U6.6, U7B.4
VRAM_A5: U6.5, U7B.7
VRAM_A6: U6.4, U7B.9
VRAM_A7: U6.3, U7B.12
VRAM_A8: U6.25, U7C.4
VRAM_A9: U6.24, U7C.7
VRAM_A10: U6.21, U7C.9
VRAM_A11: U6.23, U7C.12
XTAL328: Cxtal5a.1, U328.9, Y5.1
XTAL328b: Cxtal5b.1, U328.10, Y5.2
XTAL1284: Cxtal4a.1, U1284.13, Y4.1
XTAL1284b: Cxtal4b.1, U1284.12, Y4.2
YTRAP: Lytrap.1, U725.12
YTRAP_MID: Cytrap.1, Lytrap.2
